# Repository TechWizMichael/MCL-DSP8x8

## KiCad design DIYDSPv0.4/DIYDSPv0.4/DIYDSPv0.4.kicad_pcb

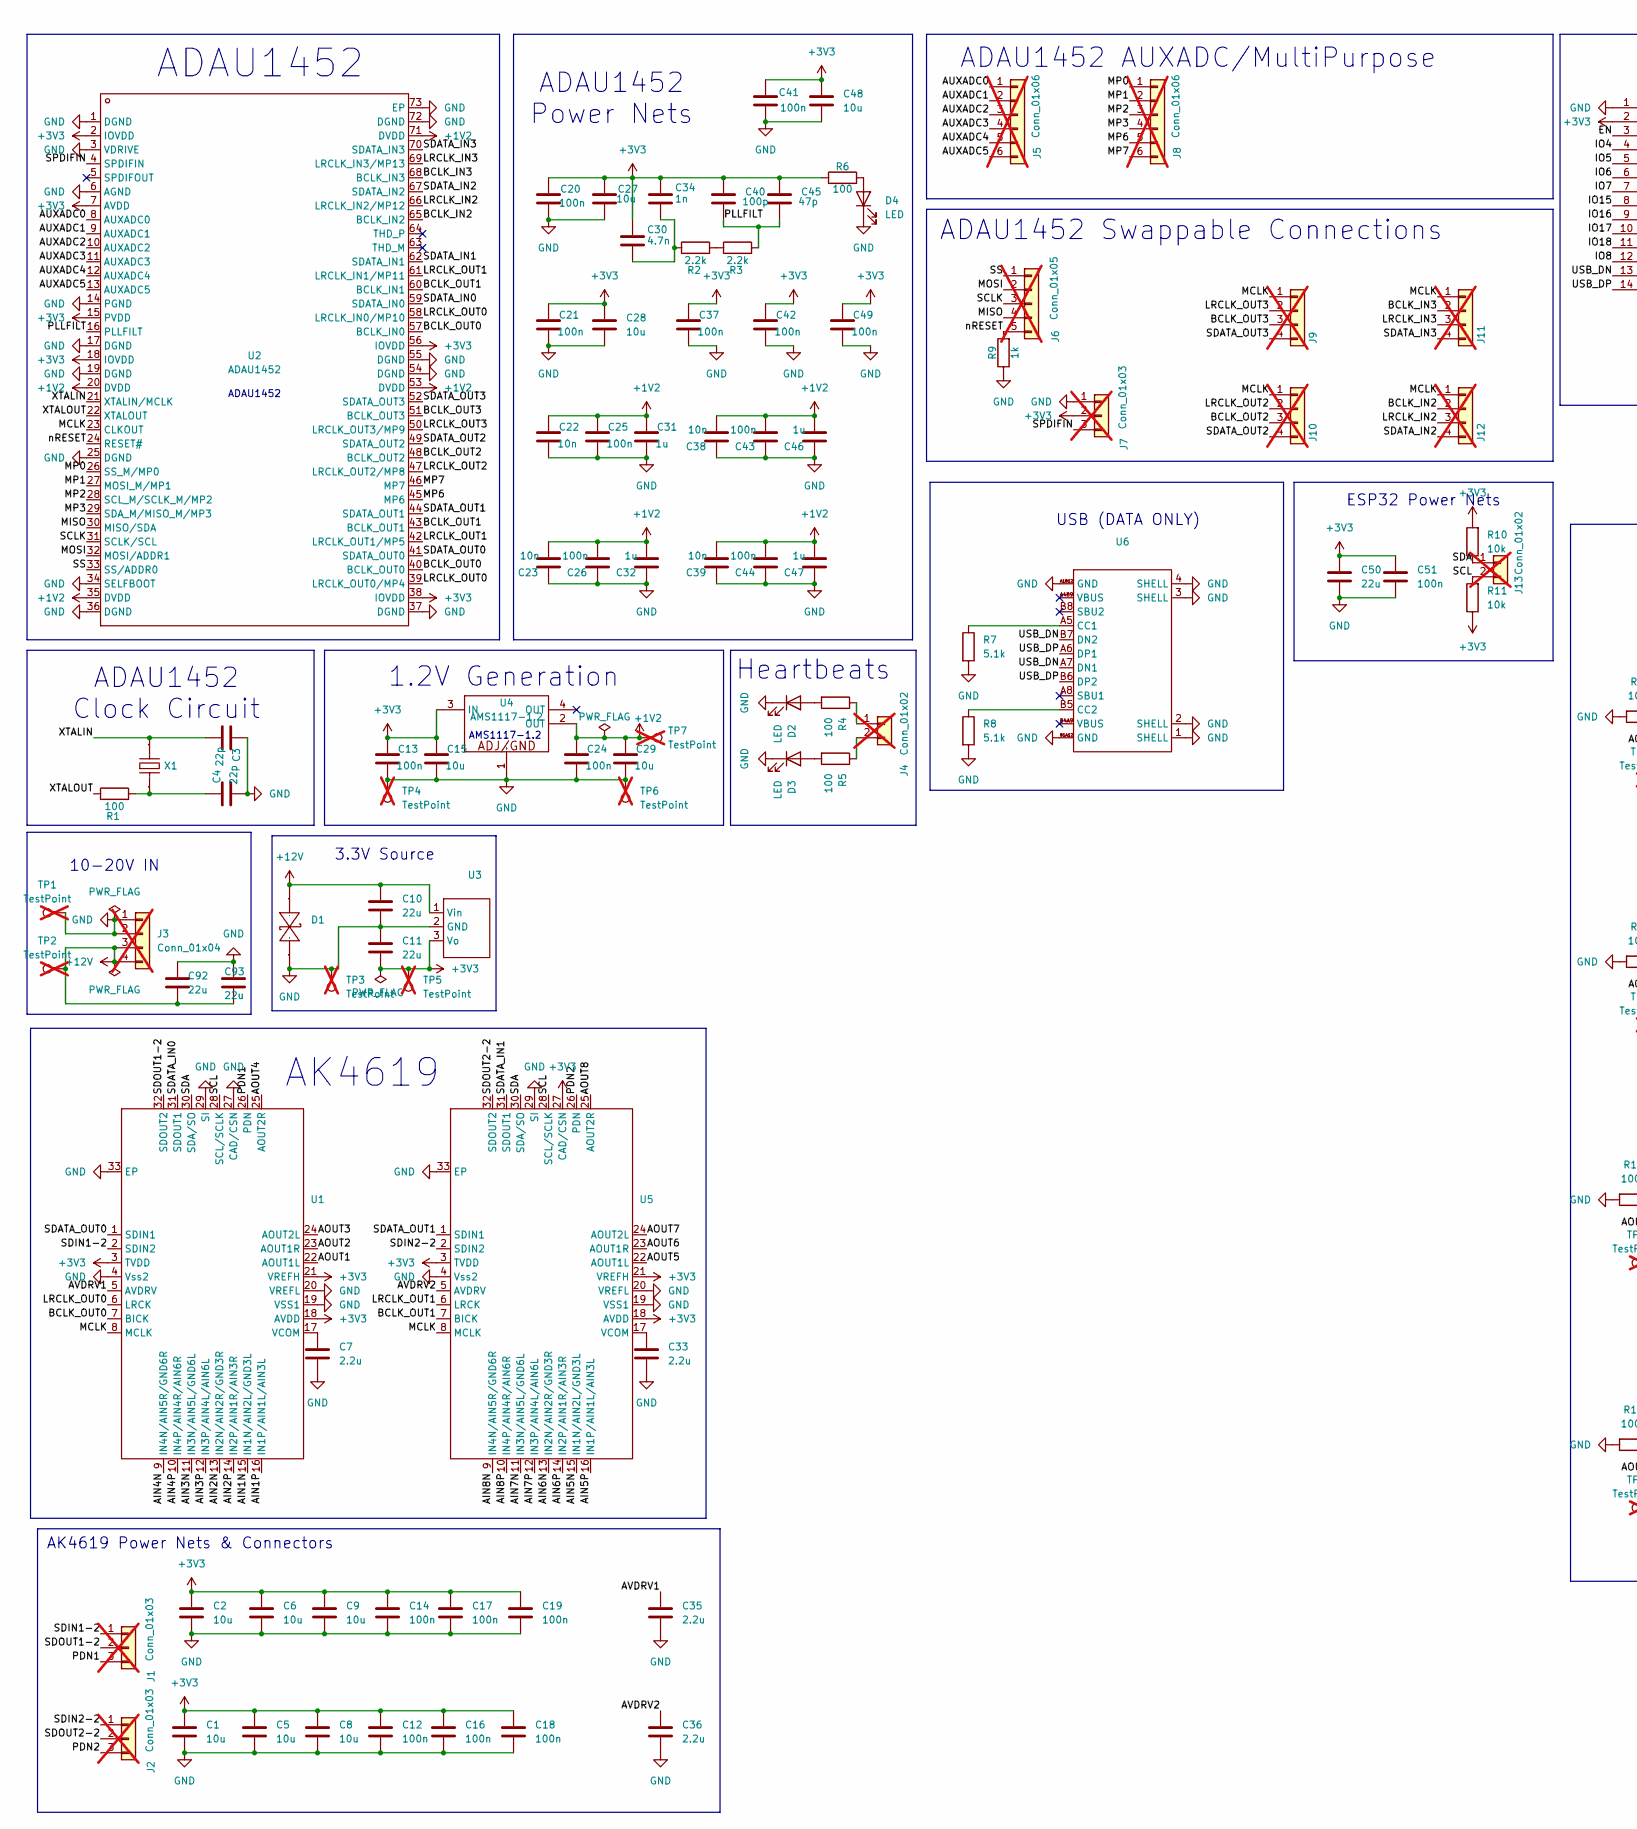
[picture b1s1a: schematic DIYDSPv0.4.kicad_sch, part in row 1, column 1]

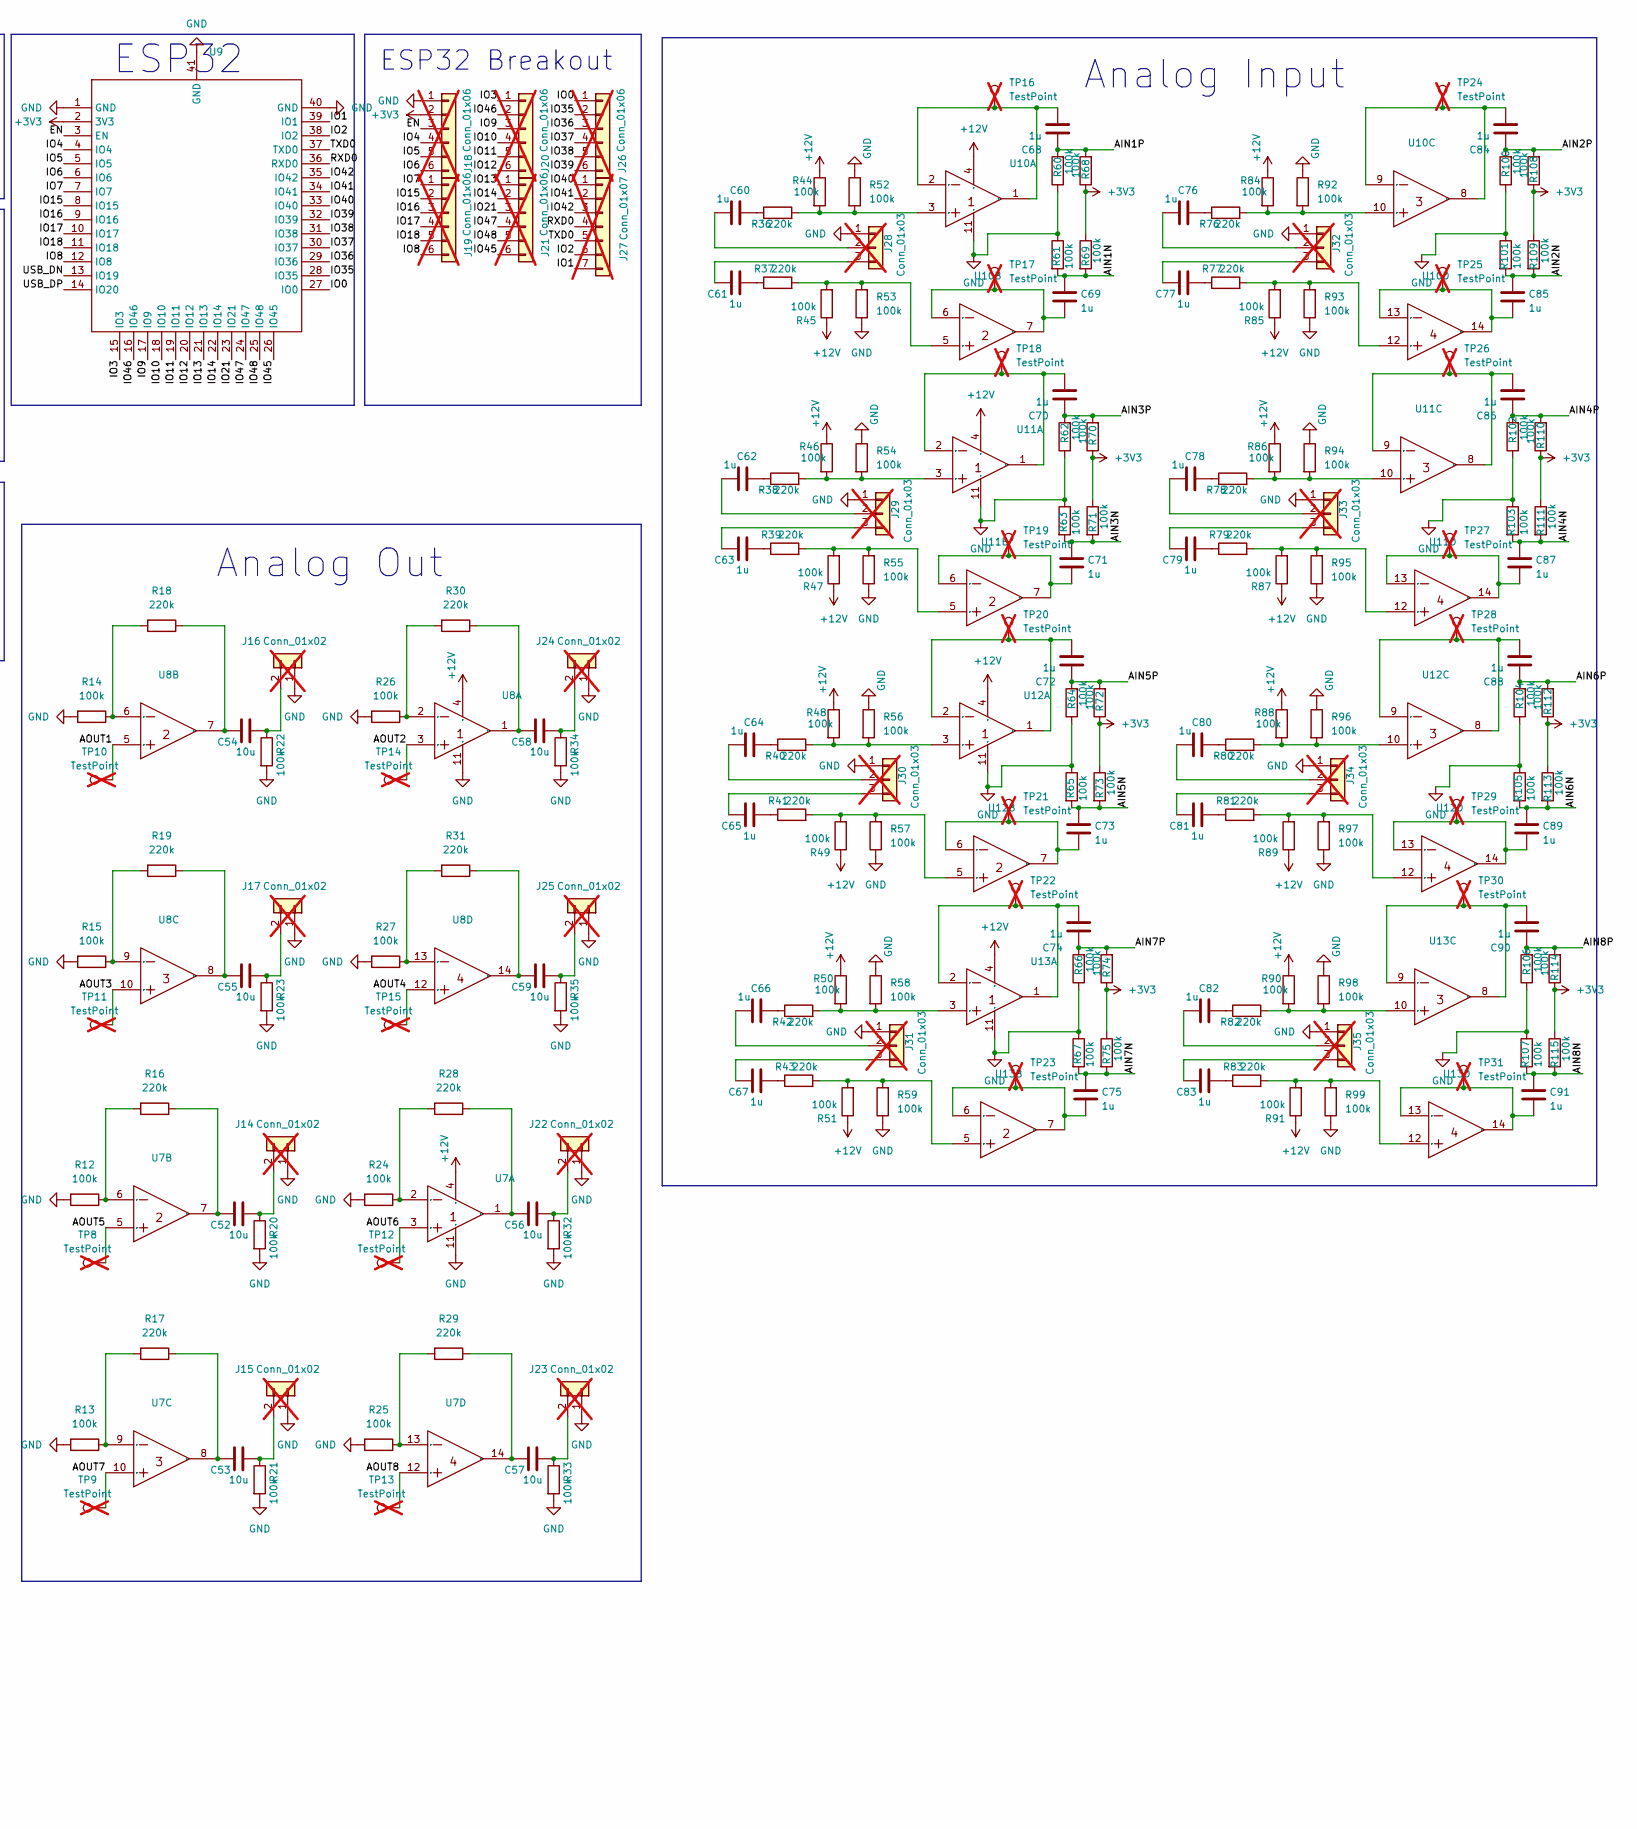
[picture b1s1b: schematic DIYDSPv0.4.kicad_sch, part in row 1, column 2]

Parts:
C1, C2, C5, C6, C8, C9, C15, C27, C28, C29, C48, C52, C53, C54, C55, C56, C57, C58, C59: 10u; C_0603_1608Metric; LCSC Part # C96446
C3, C4: 22p; C_0402_1005Metric; LCSC Part # C1555
C7, C33, C35, C36: 2.2u; C_0402_1005Metric; LCSC Part # C12530
C10, C11, C50, C92, C93: 22u; C_0805_2012Metric; LCSC Part # C45783
C12, C13, C14, C16, C17, C18, C19, C20, C21, C24, C25, C26, C37, C41, C42, C43, C44, C49, C51: 100n; C_0402_1005Metric; LCSC Part # C307331
C22, C23, C38, C39: 10n; C_0402_1005Metric; LCSC Part # C15195
C30: 4.7n; C_0402_1005Metric; LCSC Part # C1538
C31, C32, C46, C47, C60, C61, C62, C63, C64, C65, C66, C67, C68, C69, C70, C71, C72, C73, C74, C75, C76, C77, C78, C79, C80, C81, C82, C83, C84, C85, C86, C87, C88, C89, C90, C91: 1u; C_0402_1005Metric; LCSC Part # C52923
C34: 1n; C_0402_1005Metric; LCSC Part # C1523
C40: 100p; C_0402_1005Metric; LCSC Part # C1546
C45: 47p; C_0402_1005Metric; LCSC Part # C1567
D1: SMF20CA; Manufacturer Part SMF20CA; LCSC Part Name 双向TVS 20V截止 峰值浪涌电流：6.2A
D2, D3, D4: LED; LED_0805_2012Metric; LCSC Part # C84256
J1, J2, J7, J28, J29, J30, J31, J32, J33, J34, J35: Conn_01x03; PinHeader_1x03_P2.54mm_Vertical; not fitted
J3, J9, J10, J11, J12: Conn_01x04; PinHeader_1x04_P2.54mm_Vertical; not fitted
J4, J13, J14, J15, J16, J17, J22, J23, J24, J25: Conn_01x02; PinHeader_1x02_P2.54mm_Vertical; not fitted
J5, J8, J18, J19, J20, J21, J26: Conn_01x06; PinHeader_1x06_P2.54mm_Vertical; not fitted
J6: Conn_01x05; PinHeader_1x05_P2.54mm_Vertical; not fitted
J27: Conn_01x07; PinHeader_1x07_P2.54mm_Vertical; not fitted
R1, R4, R5, R6: 100; C_0805_2012Metric; LCSC Part # C17408
R2, R3: 2.2k; R_0402_1005Metric; LCSC Part # C25879
R7, R8: 5.1k; R_0402_1005Metric; LCSC Part # C25905
R9: 1k; R_0402_1005Metric; LCSC Part # C11702
R10, R11: 10k; R_0402_1005Metric; LCSC Part # C25744
R12, R13, R14, R15, R20, R21, R22, R23, R24, R25, R26, R27, R32, R33, R34, R35, R44, R45, R46, R47, R48, R49, R50, R51, R52, R53, R54, R55, R56, R57, R58, R59, R60, R61, R62, R63, R64, R65, R66, R67, R68, R69, R70, R71, R72, R73, R74, R75, R84, R85, R86, R87, R88, R89, R90, R91, R92, R93, R94, R95, R96, R97, R98, R99, R100, R101, R102, R103, R104, R105, R106, R107, R108, R109, R110, R111, R112, R113, R114, R115: 100k; R_0402_1005Metric; LCSC Part # C25741
R16, R17, R18, R19, R28, R29, R30, R31, R36, R37, R38, R39, R40, R41, R42, R43, R76, R77, R78, R79, R80, R81, R82, R83: 220k; C_0603_1608Metric; LCSC Part # C22961
TP1, TP3, TP4, TP6: TestPoint; TestPoint_THTPad_D4.0mm_Drill2.0mm; not fitted
TP2, TP5, TP7, TP8, TP9, TP10, TP11, TP12, TP13, TP14, TP15, TP16, TP17, TP18, TP19, TP20, TP21, TP22, TP23, TP24, TP25, TP26, TP27, TP28, TP29, TP30, TP31: TestPoint; TestPoint_THTPad_D2.0mm_Drill1.0mm; not fitted
U1, U5: AK4619VN; Manufacturer Part AK4619VN; LCSC Part Name AK4619VN
U2: ADAU1452; ADAU1452WBCPZ-RL; Manufacturer Part ADAU1452WBCPZ-RL; LCSC Part Name SigmaDSP 数字音频处理器
U3: K7803M-1000R3; Manufacturer Part K7803M-1000R3; LCSC Part Name DCDC电源模块
U4: AMS1117-1.2; Manufacturer Part AMS1117-1.2; LCSC Part Name 1.2V 1A 15V
U6: GT-USB-7010ASV; Manufacturer Part GT-USB-7010ASV; LCSC Part Name Type-C 母 卧贴
U7, U8, U10, U11, U12, U13: LM324DT; Manufacturer Part LM324DT; LCSC Part Name 低功耗四路运算放大器
U9: ESP32-S3-WROOM-1U-N8; Manufacturer Part ESP32-S3-WROOM-1U-N8; LCSC Part Name 通用型Wi-Fi+低功耗蓝牙MCU模组
X1: 12.288MHz; S47SMD12.288M20PF20R30B3; Manufacturer Part S47SMD12.288M20PF20R30B3; LCSC Part Name 12.288MHz ±20ppm 20pF

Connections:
+1V2: C22.1, C23.2, C24.1, C25.1, C26.2, C29.1, C31.1, C32.2, C38.2, C39.2, C43.2, C44.2, C46.2, C47.2, TP7.1, U2.20 (DVDD), U2.35 (DVDD), U2.53 (DVDD), U2.71 (DVDD), U4.2 (OUT)
+3V3: C1.2, C2.1, C5.2, C6.1, C8.1, C9.1, C11.1, C12.2, C13.1, C14.2, C15.1, C16.2, C17.2, C18.2, C19.2, C20.1, C21.1, C27.1, C28.1, C30.1, C34.1, C37.1, C40.1, C41.1, C42.1, C45.1, C48.1, C49.1, C50.1, C51.1, J7.2, J18.2, R6.1, R10.2, R11.1, R68.1, R69.1, R70.1, R71.1, R72.1, R73.1, R74.1, R75.1, R108.1, R109.1, R110.1, R111.1, R112.1, R113.1, R114.1, R115.1, TP5.1, U1.3 (TVDD), U1.18 (AVDD), U1.21 (VREFH), U2.2 (IOVDD), U2.7 (AVDD), U2.15 (PVDD), U2.18 (IOVDD), U2.38 (IOVDD), U2.56 (IOVDD), U3.3 (Vo), U4.3 (IN), U5.3 (TVDD), U5.18 (AVDD), U5.21 (VREFH), U5.27 (CAD/CSN), U9.2 (3V3)
+12V: C10.1, C92.2, C93.2, D1.2, J3.3, J3.4, R44.1, R45.1, R46.1, R47.1, R48.1, R49.1, R50.1, R51.1, R84.1, R85.1, R86.1, R87.1, R88.1, R89.1, R90.1, R91.1, TP2.1, U3.1 (Vin), U7.4 (VCC+), U8.4 (VCC+), U10.4 (VCC+), U11.4 (VCC+), U12.4 (VCC+), U13.4 (VCC+)
/AIN1N: C69.2, R61.2, R69.2, U1.15 (IN1N/AIN2L/GND3L)
/AIN1P: C68.2, R60.2, R68.2, U1.16 (IN1P/AIN1L/AIN3L)
/AIN2N: C85.2, R101.2, R109.2, U1.13 (IN2N/AIN2R/GND3R)
/AIN2P: C84.2, R100.2, R108.2, U1.14 (IN2P/AIN1R/AIN3R)
/AIN3N: C71.2, R63.2, R71.2, U1.11 (IN3N/AIN5L/GND6L)
/AIN3P: C70.2, R62.2, R70.2, U1.12 (IN3P/AIN4L/AIN6L)
/AIN4N: C87.2, R103.2, R111.2, U1.9 (IN4N/AIN5R/GND6R)
/AIN4P: C86.2, R102.2, R110.2, U1.10 (IN4P/AIN4R/AIN6R)
/AIN5N: C73.2, R65.2, R73.2, U5.15 (IN1N/AIN2L/GND3L)
/AIN5P: C72.2, R64.2, R72.2, U5.16 (IN1P/AIN1L/AIN3L)
/AIN6N: C89.2, R105.2, R113.2, U5.13 (IN2N/AIN2R/GND3R)
/AIN6P: C88.2, R104.2, R112.2, U5.14 (IN2P/AIN1R/AIN3R)
/AIN7N: C75.2, R67.2, R75.2, U5.11 (IN3N/AIN5L/GND6L)
/AIN7P: C74.2, R66.2, R74.2, U5.12 (IN3P/AIN4L/AIN6L)
/AIN8N: C91.2, R107.2, R115.2, U5.9 (IN4N/AIN5R/GND6R)
/AIN8P: C90.2, R106.2, R114.2, U5.10 (IN4P/AIN4R/AIN6R)
/AOUT1: TP10.1, U1.22 (AOUT1L), U8.5 (IN2+)
/AOUT2: TP14.1, U1.23 (AOUT1R), U8.3 (IN1+)
/AOUT3: TP11.1, U1.24 (AOUT2L), U8.10 (IN3+)
/AOUT4: TP15.1, U1.25 (AOUT2R), U8.12 (IN4+)
/AOUT5: TP8.1, U5.22 (AOUT1L), U7.5 (IN2+)
/AOUT6: TP12.1, U5.23 (AOUT1R), U7.3 (IN1+)
/AOUT7: TP9.1, U5.24 (AOUT2L), U7.10 (IN3+)
/AOUT8: TP13.1, U5.25 (AOUT2R), U7.12 (IN4+)
/AUXADC0: J5.1, U2.8 (AUXADC0)
/AUXADC1: J5.2, U2.9 (AUXADC1)
/AUXADC2: J5.3, U2.10 (AUXADC2)
/AUXADC3: J5.4, U2.11 (AUXADC3)
/AUXADC4: J5.5, U2.12 (AUXADC4)
/AUXADC5: J5.6, U2.13 (AUXADC5)
/AVDRV1: C35.2, U1.5 (AVDRV)
/AVDRV2: C36.2, U5.5 (AVDRV)
/BCLK_IN2: J12.2, U2.65 (BCLK_IN2)
/BCLK_IN3: J11.2, U2.68 (BCLK_IN3)
/BCLK_OUT0: U1.7 (BICK), U2.40 (BCLK_OUT0), U2.57 (BCLK_IN0)
/BCLK_OUT1: U2.43 (BCLK_OUT1), U2.60 (BCLK_IN1), U5.7 (BICK)
/BCLK_OUT2: J10.3, U2.48 (BCLK_OUT2)
/BCLK_OUT3: J9.3, U2.51 (BCLK_OUT3)
/EN: J18.3, U9.3 (EN)
/IO0: J26.1, U9.27 (IO0)
/IO1: J27.7, U9.39 (IO1)
/IO2: J27.6, U9.38 (IO2)
/IO3: J20.1, U9.15 (IO3)
/IO4: J18.4, U9.4 (IO4)
/IO5: J18.5, U9.5 (IO5)
/IO6: J18.6, U9.6 (IO6)
/IO7: J19.1, U9.7 (IO7)
/IO8: J19.6, U9.12 (IO8)
/IO9: J20.3, U9.17 (IO9)
/IO10: J20.4, U9.18 (IO10)
/IO11: J20.5, U9.19 (IO11)
/IO12: J20.6, U9.20 (IO12)
/IO13: J21.1, U9.21 (IO13)
/IO14: J21.2, U9.22 (IO14)
/IO15: J19.2, U9.8 (IO15)
/IO16: J19.3, U9.9 (IO16)
/IO17: J19.4, U9.10 (IO17)
/IO18: J19.5, U9.11 (IO18)
/IO21: J21.3, U9.23 (IO21)
/IO35: J26.2, U9.28 (IO35)
/IO36: J26.3, U9.29 (IO36)
/IO37: J26.4, U9.30 (IO37)
/IO38: J26.5, U9.31 (IO38)
/IO39: J26.6, U9.32 (IO39)
/IO40: J27.1, U9.33 (IO40)
/IO41: J27.2, U9.34 (IO41)
/IO42: J27.3, U9.35 (IO42)
/IO45: J21.6, U9.26 (IO45)
/IO46: J20.2, U9.16 (IO46)
/IO47: J21.4, U9.24 (IO47)
/IO48: J21.5, U9.25 (IO48)
/LRCLK_IN2: J12.3, U2.66 (LRCLK_IN2/MP12)
/LRCLK_IN3: J11.3, U2.69 (LRCLK_IN3/MP13)
/LRCLK_OUT0: U1.6 (LRCK), U2.39 (LRCLK_OUT0/MP4), U2.58 (LRCLK_IN0/MP10)
/LRCLK_OUT1: U2.42 (LRCLK_OUT1/MP5), U2.61 (LRCLK_IN1/MP11), U5.6 (LRCK)
/LRCLK_OUT2: J10.2, U2.47 (LRCLK_OUT2/MP8)
/LRCLK_OUT3: J9.2, U2.50 (LRCLK_OUT3/MP9)
/MCLK: J9.1, J10.1, J11.1, J12.1, U1.8 (MCLK), U2.23 (CLKOUT), U5.8 (MCLK)
/MISO: J6.4, U2.30 (MISO/SDA)
/MOSI: J6.2, U2.32 (MOSI/ADDR1)
/MP0: J8.1, U2.26 (SS_M/MP0)
/MP1: J8.2, U2.27 (MOSI_M/MP1)
/MP2: J8.3, U2.28 (SCL_M/SCLK_M/MP2)
/MP3: J8.4, U2.29 (SDA_M/MISO_M/MP3)
/MP6: J8.5, U2.45 (MP6)
/MP7: J8.6, U2.46 (MP7)
/PDN1: J1.3, U1.26 (PDN)
/PDN2: J2.3, U5.26 (PDN)
/PLLFILT: C40.2, C45.2, R3.2, U2.16 (PLLFILT)
/RXD0: J27.4, U9.36 (RXD0)
/SCL: J13.2, R11.2, U1.28 (SCL/SCLK), U5.28 (SCL/SCLK)
/SCLK: J6.3, U2.31 (SCLK/SCL)
/SDA: J13.1, R10.1, U1.30 (SDA/SO), U5.30 (SDA/SO)
/SDATA_IN0: U1.31 (SDOUT1), U2.59 (SDATA_IN0)
/SDATA_IN1: U2.62 (SDATA_IN1), U5.31 (SDOUT1)
/SDATA_IN2: J12.4, U2.67 (SDATA_IN2)
/SDATA_IN3: J11.4, U2.70 (SDATA_IN3)
/SDATA_OUT0: U1.1 (SDIN1), U2.41 (SDATA_OUT0)
/SDATA_OUT1: U2.44 (SDATA_OUT1), U5.1 (SDIN1)
/SDATA_OUT2: J10.4, U2.49 (SDATA_OUT2)
/SDATA_OUT3: J9.4, U2.52 (SDATA_OUT3)
/SDIN1-2: J1.1, U1.2 (SDIN2)
/SDIN2-2: J2.1, U5.2 (SDIN2)
/SDOUT1-2: J1.2, U1.32 (SDOUT2)
/SDOUT2-2: J2.2, U5.32 (SDOUT2)
/SPDIFIN: J7.3, U2.4 (SPDIFIN)
/SS: J6.1, U2.33 (SS/ADDR0)
/TXD0: J27.5, U9.37 (TXD0)
/USB_DN: U6.A7 (DN1), U6.B7 (DN2), U9.13 (IO19)
/USB_DP: U6.A6 (DP1), U6.B6 (DP2), U9.14 (IO20)
/XTALIN: C3.2, U2.21 (XTALIN/MCLK), X1.2
/XTALOUT: R1.1, U2.22 (XTALOUT)
/nRESET: J6.5, R9.2, U2.24 (RESET#)
GND: C1.1, C2.2, C3.1, C4.2, C5.1, C6.2, C7.1, C8.2, C9.2, C10.2, C11.2, C12.1, C13.2, C14.1, C15.2, C16.1, C17.1, C18.1, C19.1, C20.2, C21.2, C22.2, C23.1, C24.2, C25.2, C26.1, C27.2, C28.2, C29.2, C31.2, C32.1, C33.1, C35.1, C36.1, C37.2, C38.1, C39.1, C41.2, C42.2, C43.1, C44.1, C46.1, C47.1, C48.2, C49.2, C50.2, C51.2, C92.1, C93.1, D1.1, D2.1 (K), D3.1 (K), D4.1 (K), J3.1, J3.2, J7.1, J14.1, J15.1, J16.1, J17.1, J18.1, J22.1, J23.1, J24.1, J25.1, J28.1, J29.1, J30.1, J31.1, J32.1, J33.1, J34.1, J35.1, R7.2, R8.2, R9.1, R12.2, R13.2, R14.2, R15.2, R20.2, R21.2, R22.2, R23.2, R24.2, R25.2, R26.2, R27.2, R32.2, R33.2, R34.2, R35.2, R52.1, R53.1, R54.1, R55.1, R56.1, R57.1, R58.1, R59.1, R60.1, R61.1, R62.1, R63.1, R64.1, R65.1, R66.1, R67.1, R92.1, R93.1, R94.1, R95.1, R96.1, R97.1, R98.1, R99.1, R100.1, R101.1, R102.1, R103.1, R104.1, R105.1, R106.1, R107.1, TP1.1, TP3.1, TP4.1, TP6.1, U1.4 (Vss2), U1.19 (VSS1), U1.20 (VREFL), U1.27 (CAD/CSN), U1.29 (SI), U1.33 (EP), U2.1 (DGND), U2.3 (VDRIVE), U2.6 (AGND), U2.14 (PGND), U2.17 (DGND), U2.19 (DGND), U2.25 (DGND), U2.34 (SELFBOOT), U2.36 (DGND), U2.37 (DGND), U2.54 (DGND), U2.55 (DGND), U2.72 (DGND), U2.73 (EP), U3.2 (GND), U4.1 (ADJ/GND), U5.4 (Vss2), U5.19 (VSS1), U5.20 (VREFL), U5.29 (SI), U5.33 (EP), U6.1 (SHELL), U6.2 (SHELL), U6.3 (SHELL), U6.4 (SHELL), U6.A1B12 (GND), U6.B1A12 (GND), U7.11 (VCC-), U8.11 (VCC-), U9.1 (GND), U9.40 (GND), U9.41 (GND), U10.11 (VCC-), U11.11 (VCC-), U12.11 (VCC-), U13.11 (VCC-)
unnamed: C4.1, R1.2, X1.1
unnamed: C30.2, C34.2, R2.1
unnamed: C60.2, R36.1
unnamed: C61.2, R37.1
unnamed: C62.2, R38.1
unnamed: C63.2, R39.1
unnamed: C64.2, R40.1
unnamed: C65.2, R41.1
unnamed: C66.2, R42.1
unnamed: C67.2, R43.1
unnamed: C76.2, R76.1
unnamed: C77.2, R77.1
unnamed: C78.2, R78.1
unnamed: C79.2, R79.1
unnamed: C80.2, R80.1
unnamed: C81.2, R81.1
unnamed: C82.2, R82.1
unnamed: C83.2, R83.1
unnamed: D2.2 (A), R4.2
unnamed: D3.2 (A), R5.2
unnamed: D4.2 (A), R6.2
unnamed: J4.1, R4.1
unnamed: J4.2, R5.1
unnamed: C52.2, J14.2, R20.1
unnamed: C53.2, J15.2, R21.1
unnamed: C54.2, J16.2, R22.1
unnamed: C55.2, J17.2, R23.1
unnamed: C56.2, J22.2, R32.1
unnamed: C57.2, J23.2, R33.1
unnamed: C58.2, J24.2, R34.1
unnamed: C59.2, J25.2, R35.1
unnamed: C60.1, J28.2
unnamed: C61.1, J28.3
unnamed: C62.1, J29.2
unnamed: C63.1, J29.3
unnamed: C64.1, J30.2
unnamed: C65.1, J30.3
unnamed: C66.1, J31.2
unnamed: C67.1, J31.3
unnamed: C76.1, J32.2
unnamed: C77.1, J32.3
unnamed: C78.1, J33.2
unnamed: C79.1, J33.3
unnamed: C80.1, J34.2
unnamed: C81.1, J34.3
unnamed: C82.1, J35.2
unnamed: C83.1, J35.3
unnamed: R2.2, R3.1
unnamed: C7.2, U1.17 (VCOM)
unnamed: C33.2, U5.17 (VCOM)
unnamed: R7.1, U6.A5 (CC1)
unnamed: R8.1, U6.B5 (CC2)
unnamed: R24.1, R28.2, U7.2 (IN1-)
unnamed: C56.1, R28.1, U7.1 (OUT1)
unnamed: R12.1, R16.2, U7.6 (IN2-)
unnamed: C52.1, R16.1, U7.7 (OUT2)
unnamed: R13.1, R17.2, U7.9 (IN3-)
unnamed: C53.1, R17.1, U7.8 (OUT3)
unnamed: R25.1, R29.2, U7.13 (IN4-)
unnamed: C57.1, R29.1, U7.14 (OUT4)
unnamed: R26.1, R30.2, U8.2 (IN1-)
unnamed: C58.1, R30.1, U8.1 (OUT1)
unnamed: R14.1, R18.2, U8.6 (IN2-)
unnamed: C54.1, R18.1, U8.7 (OUT2)
unnamed: R15.1, R19.2, U8.9 (IN3-)
unnamed: C55.1, R19.1, U8.8 (OUT3)
unnamed: R27.1, R31.2, U8.13 (IN4-)
unnamed: C59.1, R31.1, U8.14 (OUT4)
unnamed: R36.2, R44.2, R52.2, U10.3 (IN1+)
unnamed: C68.1, TP16.1, U10.1 (OUT1), U10.2 (IN1-)
unnamed: R37.2, R45.2, R53.2, U10.5 (IN2+)
unnamed: C69.1, TP17.1, U10.6 (IN2-), U10.7 (OUT2)
unnamed: R76.2, R84.2, R92.2, U10.10 (IN3+)
unnamed: C84.1, TP24.1, U10.8 (OUT3), U10.9 (IN3-)
unnamed: R77.2, R85.2, R93.2, U10.12 (IN4+)
unnamed: C85.1, TP25.1, U10.13 (IN4-), U10.14 (OUT4)
unnamed: R38.2, R46.2, R54.2, U11.3 (IN1+)
unnamed: C70.1, TP18.1, U11.1 (OUT1), U11.2 (IN1-)
unnamed: R39.2, R47.2, R55.2, U11.5 (IN2+)
unnamed: C71.1, TP19.1, U11.6 (IN2-), U11.7 (OUT2)
unnamed: R78.2, R86.2, R94.2, U11.10 (IN3+)
unnamed: C86.1, TP26.1, U11.8 (OUT3), U11.9 (IN3-)
unnamed: R79.2, R87.2, R95.2, U11.12 (IN4+)
unnamed: C87.1, TP27.1, U11.13 (IN4-), U11.14 (OUT4)
unnamed: R40.2, R48.2, R56.2, U12.3 (IN1+)
unnamed: C72.1, TP20.1, U12.1 (OUT1), U12.2 (IN1-)
unnamed: R41.2, R49.2, R57.2, U12.5 (IN2+)
unnamed: C73.1, TP21.1, U12.6 (IN2-), U12.7 (OUT2)
unnamed: R80.2, R88.2, R96.2, U12.10 (IN3+)
unnamed: C88.1, TP28.1, U12.8 (OUT3), U12.9 (IN3-)
unnamed: R81.2, R89.2, R97.2, U12.12 (IN4+)
unnamed: C89.1, TP29.1, U12.13 (IN4-), U12.14 (OUT4)
unnamed: R42.2, R50.2, R58.2, U13.3 (IN1+)
unnamed: C74.1, TP22.1, U13.1 (OUT1), U13.2 (IN1-)
unnamed: R43.2, R51.2, R59.2, U13.5 (IN2+)
unnamed: C75.1, TP23.1, U13.6 (IN2-), U13.7 (OUT2)
unnamed: R82.2, R90.2, R98.2, U13.10 (IN3+)
unnamed: C90.1, TP30.1, U13.8 (OUT3), U13.9 (IN3-)
unnamed: R83.2, R91.2, R99.2, U13.12 (IN4+)
unnamed: C91.1, TP31.1, U13.13 (IN4-), U13.14 (OUT4)

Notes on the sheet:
ESP32 Power Nets
Analog Out
ESP32
ADAU1452
ADAU1452 Swappable Connections
ADAU1452 Power Nets
1.2V Generation
AK4619 Power Nets & Connectors
AMS1117-1.2
Heartbeats
USB (DATA ONLY)
ESP32 Breakout
AK4619
3.3V Source
ADAU1452 AUXADC/MultiPurpose
ADAU1452 Clock Circuit
10-20V IN
Analog Input

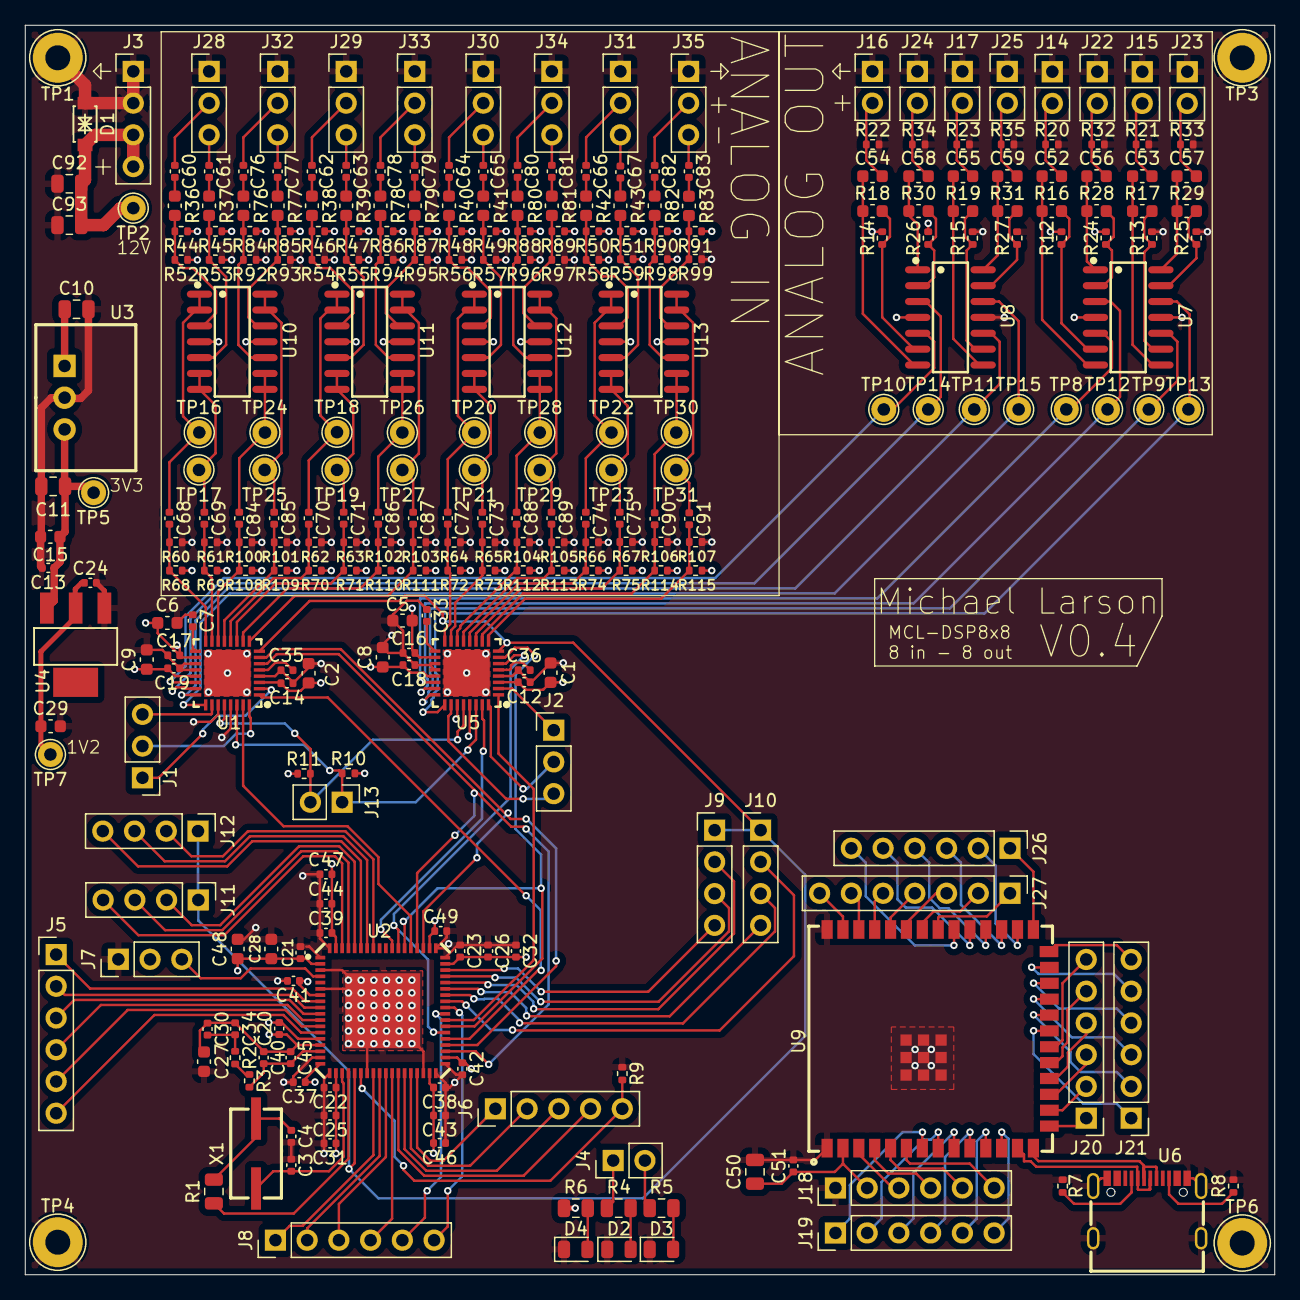
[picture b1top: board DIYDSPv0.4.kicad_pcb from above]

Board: 4 copper layers, 100.0 x 100.0 mm, 292 parts (0 on the bottom side), 217 nets.

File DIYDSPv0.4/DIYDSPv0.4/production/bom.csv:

Designator,Footprint,Quantity,Value,LCSC Part #
"C1, C15, C2, C27, C28, C29, C48, C5, C52, C53, C54, C55, C56, C57, C58, C59, C6, C8, C9",0603,19,10u,C96446
"C10, C11, C50, C92, C93",0805,5,22u,C45783
"C12, C13, C14, C16, C17, C18, C19, C20, C21, C24, C25, C26, C37, C41, C42, C43, C44, C49, C51",0402,19,100n,C307331
"C22, C23, C38, C39",0402,4,10n,C15195
"C3, C4",0402,2,22p,C1555
C30,0402,1,4.7n,C1538
"C31, C32, C46, C47, C60, C61, C62, C63, C64, C65, C66, C67, C68, C69, C70, C71, C72, C73, C74, C75, C76, C77, C78, C79, C80, C81, C82, C83, C84, C85, C86, C87, C88, C89, C90, C91",0402,36,1u,C52923
"C33, C35, C36, C7",0402,4,2.2u,C12530
C34,0402,1,1n,C1523
C40,0402,1,100p,C1546
C45,0402,1,47p,C1567
D1,SMF20CA,1,~,C42371747
"D2, D3, D4",0805,3,LED,C84256
"R1, R4, R5, R6",0805,4,100, C17408
"R10, R11",0402,2,10k,C25744
"R100, R101, R102, R103, R104, R105, R106, R107, R108, R109, R110, R111, R112, R113, R114, R115, R12, R13, R14, R15, R20, R21, R22, R23, R24, R25, R26, R27, R32, R33, R34, R35, R44, R45, R46, R47, R48, R49, R50, R51, R52, R53, R54, R55, R56, R57, R58, R59, R60, R61, R62, R63, R64, R65, R66, R67, R68, R69, R70, R71, R72, R73, R74, R75, R84, R85, R86, R87, R88, R89, R90, R91, R92, R93, R94, R95, R96, R97, R98, R99",0402,80,100k,C25741
"R16, R17, R18, R19, R28, R29, R30, R31, R36, R37, R38, R39, R40, R41, R42, R43, R76, R77, R78, R79, R80, R81, R82, R83",0603,24,220k, C22961
"R2, R3",0402,2,2.2k, C25879
"R7, R8",0402,2,5.1k, C25905
R9,0402,1,1k,C11702
"U1, U5",AK4619VN,2,~,C3034747
"U10, U11, U12, U13, U7, U8",LM324DT,6,~,C71035
U2,ADAU1452WBCPZ-RL,1,ADAU1452,C462188
U3,K7803M-1000R3,1,~,C22749779
U4,AMS1117-1.2,1,AMS1117-1.2,C2992568
U6,GT-USB-7010ASV,1,~,C2988369
U9,ESP32-S3-WROOM-1U-N8,1,~, C2980297
X1,S47SMD12.288M20PF20R30B3,1,12.288MHz,C5346044

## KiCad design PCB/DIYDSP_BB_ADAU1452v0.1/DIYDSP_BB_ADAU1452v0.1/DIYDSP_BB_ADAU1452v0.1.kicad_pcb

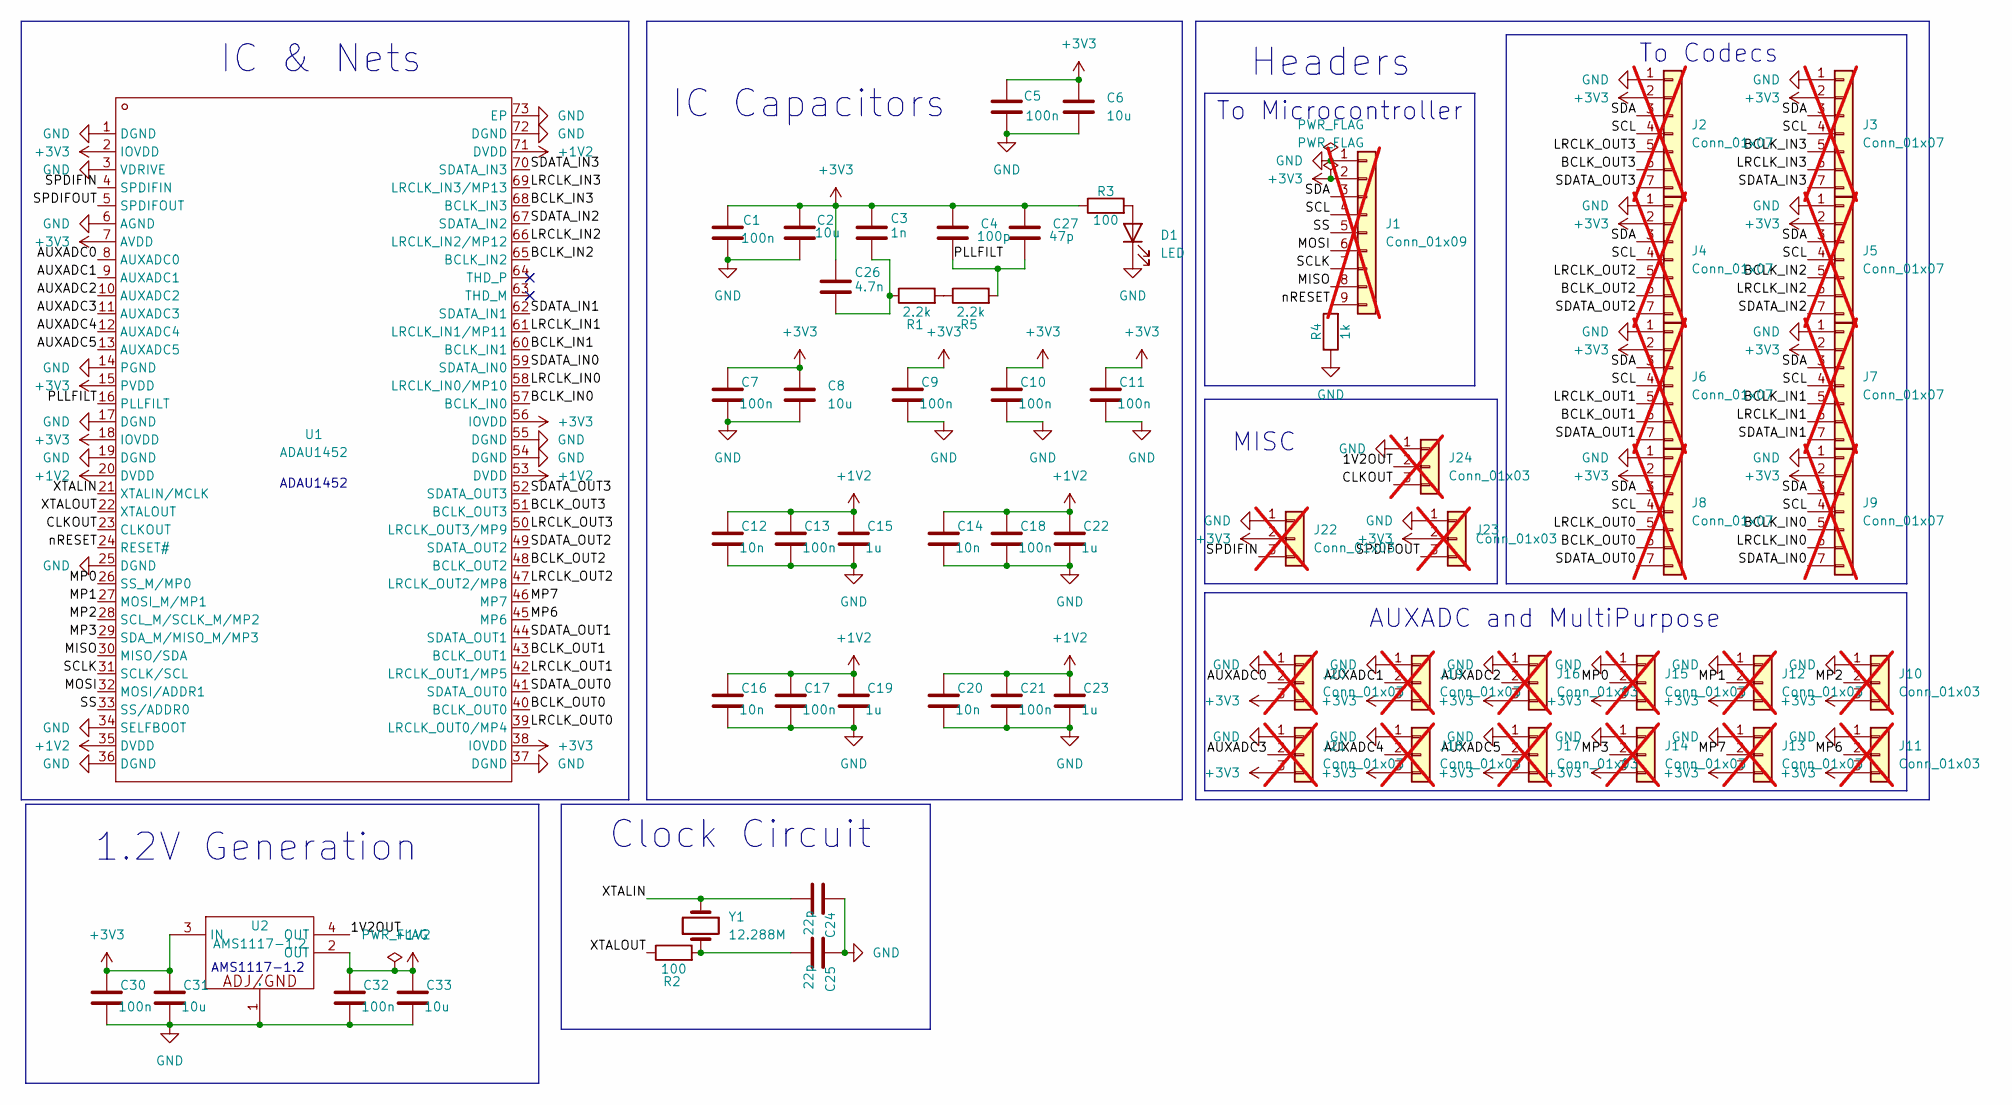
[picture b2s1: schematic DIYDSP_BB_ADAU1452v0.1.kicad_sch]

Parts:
C1, C5, C7, C9, C10, C11, C13, C17, C18, C21, C30, C32: 100n; C_0805_2012Metric; LCSC Part # C28233
C2, C6, C8, C31, C33: 10u; C_0805_2012Metric; LCSC Part # C15850
C3: 1n; C_0805_2012Metric; LCSC Part # C46653
C4: 100p; C_0805_2012Metric; LCSC Part # C1790
C12, C14, C16, C20: 10n; C_0805_2012Metric; LCSC Part # C1710
C15, C19, C22, C23: 1u; C_0805_2012Metric; LCSC Part # C28323
C24, C25: 22p; C_0805_2012Metric; LCSC Part # C1804
C26: 4.7n; C_0805_2012Metric; LCSC Part # C1744
C27: 47p; C_0805_2012Metric; LCSC Part # C14857
D1: LED; LED_0805_2012Metric; LCSC Part # C84256
J1: Conn_01x09; PinHeader_1x09_P2.54mm_Vertical; LCSC Part # C706881; not fitted
J2, J3, J4, J5, J6, J7, J8, J9: Conn_01x07; PinHeader_1x07_P2.54mm_Vertical; LCSC Part # C706879; not fitted
J10, J11, J12, J13, J14, J15, J16, J17, J18, J19, J20, J21, J22, J23, J24: Conn_01x03; PinHeader_1x03_P2.54mm_Vertical; LCSC Part # C19190477; not fitted
R1, R5: 2.2k; R_0805_2012Metric; LCSC Part # C17520
R2, R3: 100; R_0805_2012Metric; LCSC Part # C17408
R4: 1k; R_0805_2012Metric; LCSC Part # C17513
U1: ADAU1452; ADAU1452WBCPZ-RL; Manufacturer Part ADAU1452WBCPZ-RL; LCSC Part Name SigmaDSP 数字音频处理器
U2: AMS1117-1.2; Manufacturer Part AMS1117-1.2; LCSC Part Name 1.2V 1A 15V
Y1: 12.288M; Crystal_SMD_5032-2Pin_5.0x3.2mm; LCSC Part # C20624119

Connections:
+1V2: C12.1, C13.1, C14.1, C15.1, C16.1, C17.1, C18.1, C19.1, C20.1, C21.1, C22.1, C23.1, C32.1, C33.1, U1.20 (DVDD), U1.35 (DVDD), U1.53 (DVDD), U1.71 (DVDD), U2.2 (OUT)
+3V3: C1.1, C2.1, C3.1, C4.1, C5.1, C6.1, C7.1, C8.1, C9.1, C10.1, C11.1, C26.1, C27.1, C30.1, C31.1, J1.2, J2.2, J3.2, J4.2, J5.2, J6.2, J7.2, J8.2, J9.2, J10.3, J11.3, J12.3, J13.3, J14.3, J15.3, J16.3, J17.3, J18.3, J19.3, J20.3, J21.3, J22.2, J23.2, R3.1, U1.2 (IOVDD), U1.7 (AVDD), U1.15 (PVDD), U1.18 (IOVDD), U1.38 (IOVDD), U1.56 (IOVDD), U2.3 (IN)
/1V2OUT: J24.2, U2.4 (OUT)
/AUXADC0: J20.2, U1.8 (AUXADC0)
/AUXADC1: J19.2, U1.9 (AUXADC1)
/AUXADC2: J16.2, U1.10 (AUXADC2)
/AUXADC3: J21.2, U1.11 (AUXADC3)
/AUXADC4: J18.2, U1.12 (AUXADC4)
/AUXADC5: J17.2, U1.13 (AUXADC5)
/BCLK_IN0: J9.5, U1.57 (BCLK_IN0)
/BCLK_IN1: J7.5, U1.60 (BCLK_IN1)
/BCLK_IN2: J5.5, U1.65 (BCLK_IN2)
/BCLK_IN3: J3.5, U1.68 (BCLK_IN3)
/BCLK_OUT0: J8.6, U1.40 (BCLK_OUT0)
/BCLK_OUT1: J6.6, U1.43 (BCLK_OUT1)
/BCLK_OUT2: J4.6, U1.48 (BCLK_OUT2)
/BCLK_OUT3: J2.6, U1.51 (BCLK_OUT3)
/CLKOUT: J24.3, U1.23 (CLKOUT)
/LRCLK_IN0: J9.6, U1.58 (LRCLK_IN0/MP10)
/LRCLK_IN1: J7.6, U1.61 (LRCLK_IN1/MP11)
/LRCLK_IN2: J5.6, U1.66 (LRCLK_IN2/MP12)
/LRCLK_IN3: J3.6, U1.69 (LRCLK_IN3/MP13)
/LRCLK_OUT0: J8.5, U1.39 (LRCLK_OUT0/MP4)
/LRCLK_OUT1: J6.5, U1.42 (LRCLK_OUT1/MP5)
/LRCLK_OUT2: J4.5, U1.47 (LRCLK_OUT2/MP8)
/LRCLK_OUT3: J2.5, U1.50 (LRCLK_OUT3/MP9)
/MISO: J1.8, U1.30 (MISO/SDA)
/MOSI: J1.6, U1.32 (MOSI/ADDR1)
/MP0: J15.2, U1.26 (SS_M/MP0)
/MP1: J12.2, U1.27 (MOSI_M/MP1)
/MP2: J10.2, U1.28 (SCL_M/SCLK_M/MP2)
/MP3: J14.2, U1.29 (SDA_M/MISO_M/MP3)
/MP6: J11.2, U1.45 (MP6)
/MP7: J13.2, U1.46 (MP7)
/PLLFILT: C4.2, C27.2, R5.2, U1.16 (PLLFILT)
/SCL: J1.4, J2.4, J3.4, J4.4, J5.4, J6.4, J7.4, J8.4, J9.4
/SCLK: J1.7, U1.31 (SCLK/SCL)
/SDA: J1.3, J2.3, J3.3, J4.3, J5.3, J6.3, J7.3, J8.3, J9.3
/SDATA_IN0: J9.7, U1.59 (SDATA_IN0)
/SDATA_IN1: J7.7, U1.62 (SDATA_IN1)
/SDATA_IN2: J5.7, U1.67 (SDATA_IN2)
/SDATA_IN3: J3.7, U1.70 (SDATA_IN3)
/SDATA_OUT0: J8.7, U1.41 (SDATA_OUT0)
/SDATA_OUT1: J6.7, U1.44 (SDATA_OUT1)
/SDATA_OUT2: J4.7, U1.49 (SDATA_OUT2)
/SDATA_OUT3: J2.7, U1.52 (SDATA_OUT3)
/SPDIFIN: J22.3, U1.4 (SPDIFIN)
/SPDIFOUT: J23.3, U1.5 (SPDIFOUT)
/SS: J1.5, U1.33 (SS/ADDR0)
/XTALIN: C24.2, U1.21 (XTALIN/MCLK), Y1.2
/XTALOUT: R2.1, U1.22 (XTALOUT)
/nRESET: J1.9, R4.2, U1.24 (RESET#)
GND: C1.2, C2.2, C5.2, C6.2, C7.2, C8.2, C9.2, C10.2, C11.2, C12.2, C13.2, C14.2, C15.2, C16.2, C17.2, C18.2, C19.2, C20.2, C21.2, C22.2, C23.2, C24.1, C25.1, C30.2, C31.2, C32.2, C33.2, D1.1 (K), J1.1, J2.1, J3.1, J4.1, J5.1, J6.1, J7.1, J8.1, J9.1, J10.1, J11.1, J12.1, J13.1, J14.1, J15.1, J16.1, J17.1, J18.1, J19.1, J20.1, J21.1, J22.1, J23.1, J24.1, R4.1, U1.1 (DGND), U1.3 (VDRIVE), U1.6 (AGND), U1.14 (PGND), U1.17 (DGND), U1.19 (DGND), U1.25 (DGND), U1.34 (SELFBOOT), U1.36 (DGND), U1.37 (DGND), U1.54 (DGND), U1.55 (DGND), U1.72 (DGND), U1.73 (EP), U2.1 (ADJ/GND)
unnamed: C25.2, R2.2, Y1.1
unnamed: C3.2, C26.2, R1.1
unnamed: D1.2 (A), R3.2
unnamed: R1.2, R5.1

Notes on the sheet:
To Microcontroller
IC & Nets
IC Capacitors
MISC
Headers
1.2V Generation
AMS1117-1.2
ADAU1452
To Codecs
AUXADC and MultiPurpose
Clock Circuit
